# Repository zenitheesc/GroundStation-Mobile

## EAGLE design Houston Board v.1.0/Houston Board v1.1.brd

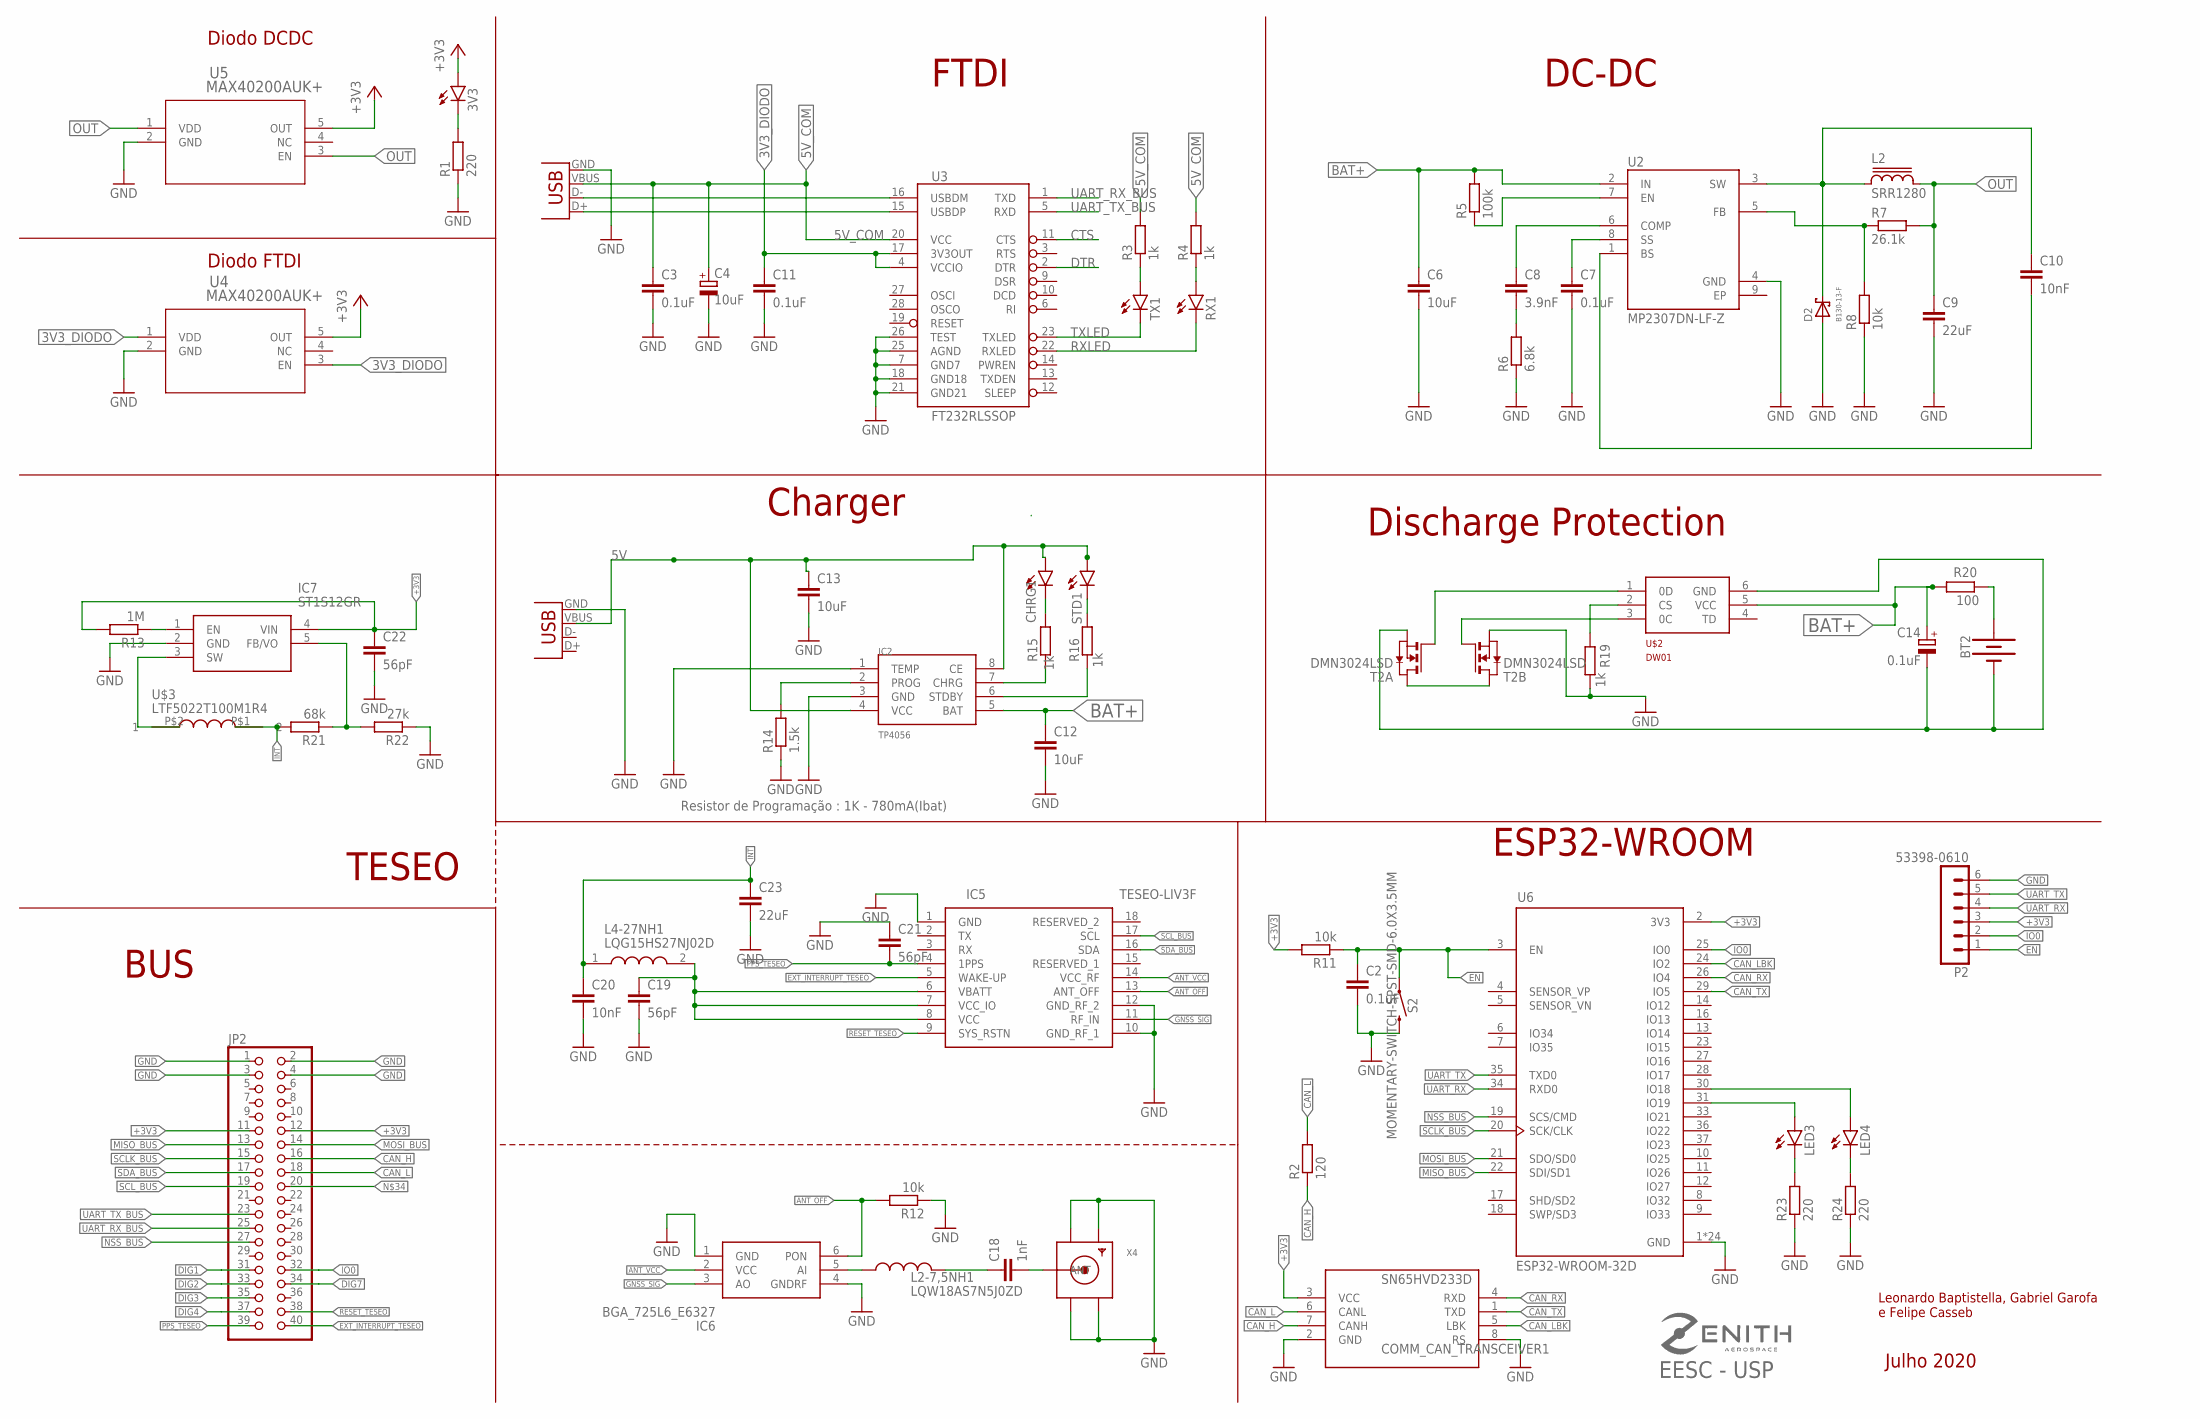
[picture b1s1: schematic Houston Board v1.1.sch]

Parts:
3V3: LEDCHIPLED_0805; CHIPLED_0805
BT2: BATTERY-18650; BATTERY_18650-HOLDER
C2: 0.1uF; C1206
C3, C7, C11: 0.1uF; C0805
C4: 10uF; PANASONIC_B
C6, C12, C13: 10uF; C0805
C8: 3.9nF; C0805
C9: 22uF; C0805
C10: 10nF; C0805
C14: 0.1uF; PANASONIC_C
C18: 1nF; C1206
C19, C21, C22: 56pF; C1206
C20: 10nF; C1206
C23: 22uF; C1206
CHRG1: LEDCHIP-LED0805; CHIP-LED0805
COMM_CAN_TRANSCEIVER1: SN65HVD233D; SOIC8
D2: B130-13-F; SMA
IC2: TP4056; SOP-8
IC5: TESEO-LIV3F; SON110P970X1010X230-18N
IC6: BGA_725L6_E6327; BGA725L6E6327
IC7: ST1S12GR; SOT95P280X110-5N
JP2: PINHD-2X20; 2X20
L2: SRR1280
L2-7,5NH1: LQW18AS7N5J0ZD; INDC1608X100N
L4-27NH1: LQG15HS27NJ02D; LQG15WH0N7B02D
LED3, LED4: LEDCHIPLED_0805; CHIPLED_0805
P2: 53398-0610
R1: 220; R0805
R2: 120; R0805
R3, R4, R15, R16, R19: 1k; R0805
R5: 100k; R0805
R6: 6.8k; R0805
R7: 26.1k; R0805
R8: 10k; R0805
R11: 10k; R1206
R12: 10k; M1206
R13: 1M; M1206
R14: 1.5k; R0805
R20: 100; R0805
R21: 68k; M1206
R22: 27k; M1206
R23, R24: 220; R1206
RX1: LEDCHIPLED_0805; CHIPLED_0805
S2: MOMENTARY-SWITCH-SPST-SMD-6.0X3.5MM; TACTILE_SWITCH_SMD_6.0X3.5MM
STD1: LEDCHIP-LED0805; CHIP-LED0805
T2: DMN3024LSD; TSSOP-8
TX1: LEDCHIPLED_0805; CHIPLED_0805
U2: MP2307DN-LF-Z; SOIC127P600X170-9N
U3: FT232RLSSOP; SSOP28DB
U4, U5: MAX40200AUK+; 21-0057F_MXM
U6: ESP32-WROOM-32D; MODULE_ESP32-WROOM-32D
U$2: DW01; SOT23-6
U$3: LTF5022T100M1R4; LTF5022T
X1, X2: USB-SMD-NS; USB-MINIB-NOSTOP
X4: SMACONNECTOR; SMA90_DIP

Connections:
3V3_DIODO: C11.1, U3.4 (VCCIO), U3.17 (3V3OUT), U4.1 (VDD), U4.3 (EN)
5V: C13.1, CHRG1.A, IC2.4 (VCC), IC2.8 (CE), STD1.A, X2.VBUS
5V_COM: C3.1, C4.+, R3.2, R4.2, U3.20 (VCC), X1.VBUS
+3V3: 3V3.A, C22.1, COMM_CAN_TRANSCEIVER1.3 (VCC), IC7.4 (VIN), JP2.11, JP2.12, P2.3, R11.2, R13.2, U4.5 (OUT), U5.5 (OUT), U6.2 (3V3)
ANT_OFF: IC5.13 (ANT_OFF), IC6.6 (PON), R12.2
ANT_VCC: IC5.14 (VCC_RF), IC6.2 (VCC)
BAT+: C6.1, C12.1, C14.+, IC2.5 (BAT), R5.2, R20.1, U2.2 (IN), U$2.5 (VCC)
CAN_H: COMM_CAN_TRANSCEIVER1.7 (CANH), JP2.16, R2.1
CAN_L: COMM_CAN_TRANSCEIVER1.6 (CANL), JP2.18, R2.2
CAN_LBK: COMM_CAN_TRANSCEIVER1.5 (LBK), U6.24 (IO2)
CAN_RX: COMM_CAN_TRANSCEIVER1.4 (RXD), U6.26 (IO4)
CAN_TX: COMM_CAN_TRANSCEIVER1.1 (TXD), U6.29 (IO5)
CTS: U3.11 (CTS)
DTR: U3.2 (DTR)
EN: C2.1, P2.1, R11.1, S2.1, U6.3 (EN)
EP: U2.9 (EP)
EXT_INTERRUPT_TESEO: IC5.5 (WAKE-UP), JP2.40
GND: C2.2, C3.2, C4.-, C6.2, C7.2, C9.2, C11.2, C12.2, C13.2, C19.2, C20.2, C21.1, C22.2, C23.2, COMM_CAN_TRANSCEIVER1.2 (GND), COMM_CAN_TRANSCEIVER1.8 (RS), D2.A, IC2.1 (TEMP), IC2.3 (GND), IC5.1 (GND), IC5.10 (GND_RF_1), IC5.12 (GND_RF_2), IC6.1 (GND), IC6.4 (GNDRF), IC7.2 (GND), JP2.1, JP2.2, JP2.3, JP2.4, P2.6, R1.1, R6.1, R8.1, R12.1, R14.1, R19.1, R22.1, R23.1, R24.1, S2.2, T2.6 (S), T2.7 (S), U2.4 (GND), U3.7 (GND7), U3.18 (GND18), U3.21 (GND21), U3.25 (AGND), U3.26 (TEST), U4.2 (GND), U5.2 (GND), U6.1 (GND), U6.15 (GND), U6.38 (GND), U6.39_1 (GND), U6.39_2 (GND), U6.39_3 (GND), U6.39_4 (GND), U6.39_5 (GND), U6.39_6 (GND), U6.39_7 (GND), U6.39_8 (GND), U6.39_9 (GND), U6.39_10 (GND), U6.39_11 (GND), U6.39_12 (GND), U6.39_13 (GND), U6.39_14 (GND), U6.39_15 (GND), U6.39_16 (GND), U6.39_17 (GND), U6.39_18 (GND), U6.39_19 (GND), U6.39_20 (GND), U6.39_21 (GND), X1.GND, X2.GND, X4.GND1, X4.GND2, X4.GND3, X4.GND4
GNSS_SIG: IC5.11 (RF_IN), IC6.3 (AO)
INT: C20.1, C23.1, L4-27NH1.1, R21.2, U$3.P$1 (2)
IO0: P2.2, U6.25 (IO0)
MISO_BUS: JP2.13, U6.22 (SDI/SD1)
MOSI_BUS: JP2.14, U6.21 (SDO/SD0)
unnamed: R5.1, U2.7 (EN)
unnamed: C8.2, R6.2
unnamed: C7.1, U2.8 (SS)
unnamed: C8.1, U2.6 (COMP)
unnamed: C10.1, D2.C, L2.1, U2.3 (SW)
unnamed: R7.1, R8.2, U2.5 (FB)
unnamed: C10.2, U2.1 (BS)
unnamed: R3.1, TX1.A
unnamed: R4.1, RX1.A
unnamed: 3V3.C, R1.2
unnamed: LED3.C, R23.2
unnamed: LED4.C, R24.2
unnamed: LED4.A, U6.30 (IO18)
unnamed: LED3.A, U6.31 (IO19)
unnamed: C19.1, IC5.6 (VBATT), IC5.7 (VCC_IO), IC5.8 (VCC), L4-27NH1.2
unnamed: C18.2, X4.ANTENNA (ANT)
unnamed: IC6.5 (AI), L2-7,5NH1.1
unnamed: IC2.2 (PROG), R14.2
unnamed: IC2.7 (CHRG), R15.1
unnamed: IC2.6 (STDBY), R16.1
unnamed: CHRG1.C, R15.2
unnamed: R16.2, STD1.C
unnamed: R19.2, U$2.2 (CS)
unnamed: BT2.PWR@1 (+), R20.2
unnamed: BT2.GND@1 (-), C14.-, T2.2 (S), T2.3 (S), U$2.6 (GND)
unnamed: T2.1 (D), T2.8 (D)
unnamed: T2.4 (G), U$2.1 (0D)
unnamed: T2.5 (G), U$2.3 (0C)
unnamed: C18.1, L2-7,5NH1.2
unnamed: IC7.1 (EN), R13.1
unnamed: IC7.3 (SW), U$3.P$2 (1)
unnamed: IC7.5 (FB/VO), R21.1, R22.2
NSS_BUS: JP2.27, U6.19 (SCS/CMD)
OUT: C9.1, L2.2, R7.2, U5.1 (VDD), U5.3 (EN)
PPS_TESEO: C21.2, IC5.4 (1PPS), JP2.39
RESET_TESEO: IC5.9 (SYS_RSTN), JP2.38
RXLED: RX1.C, U3.22 (RXLED)
SCLK_BUS: JP2.15, U6.20 (SCK/CLK)
SCL_BUS: IC5.17 (SCL), JP2.19
SDA_BUS: IC5.16 (SDA), JP2.17
TXLED: TX1.C, U3.23 (TXLED)
UART_RX: P2.4, U6.34 (RXD0)
UART_RX_BUS: JP2.25, U3.1 (TXD)
UART_TX: P2.5, U6.35 (TXD0)
UART_TX_BUS: JP2.23, U3.5 (RXD)
USB_D+1: U3.15 (USBDP), X1.D+
USB_D-1: U3.16 (USBDM), X1.D-

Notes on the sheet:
BUS
DC-DC
FTDI
Charger
Discharge Protection
TESEO
ESP32-WROOM
Resistor de Programação : 1K - 780mA(Ibat)
Diodo DCDC
Diodo FTDI
Julho 2020
Leonardo Baptistella, Gabriel Garofa e Felipe Casseb
EESC - USP

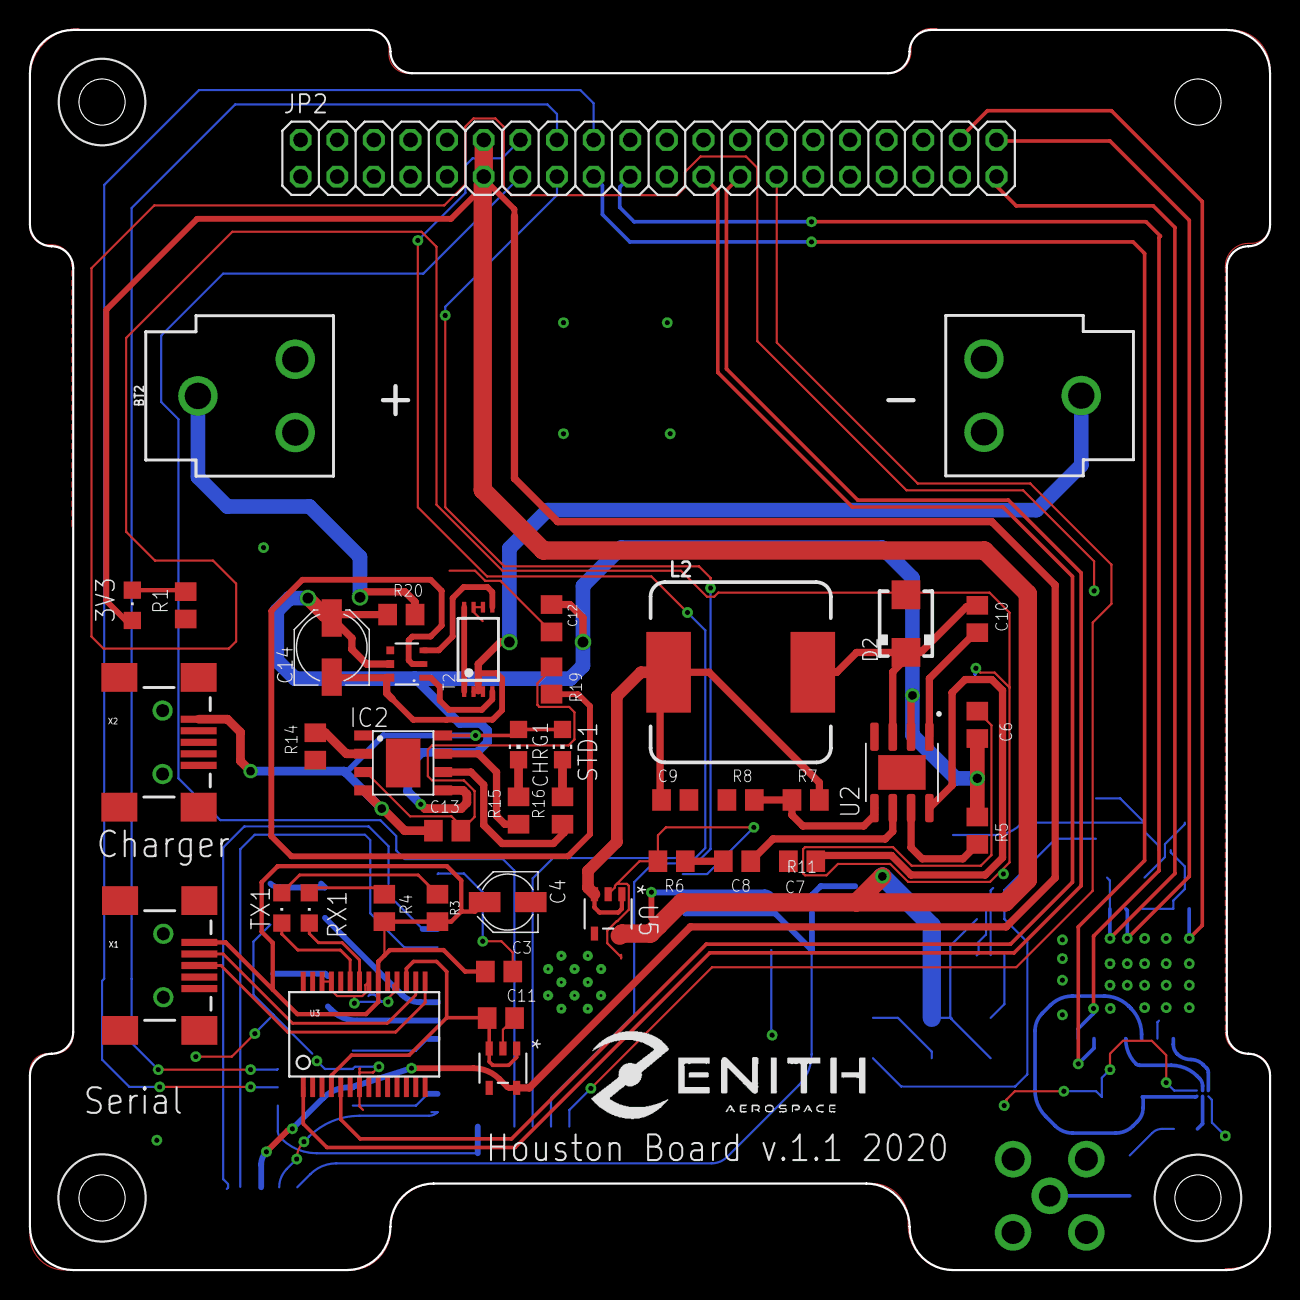
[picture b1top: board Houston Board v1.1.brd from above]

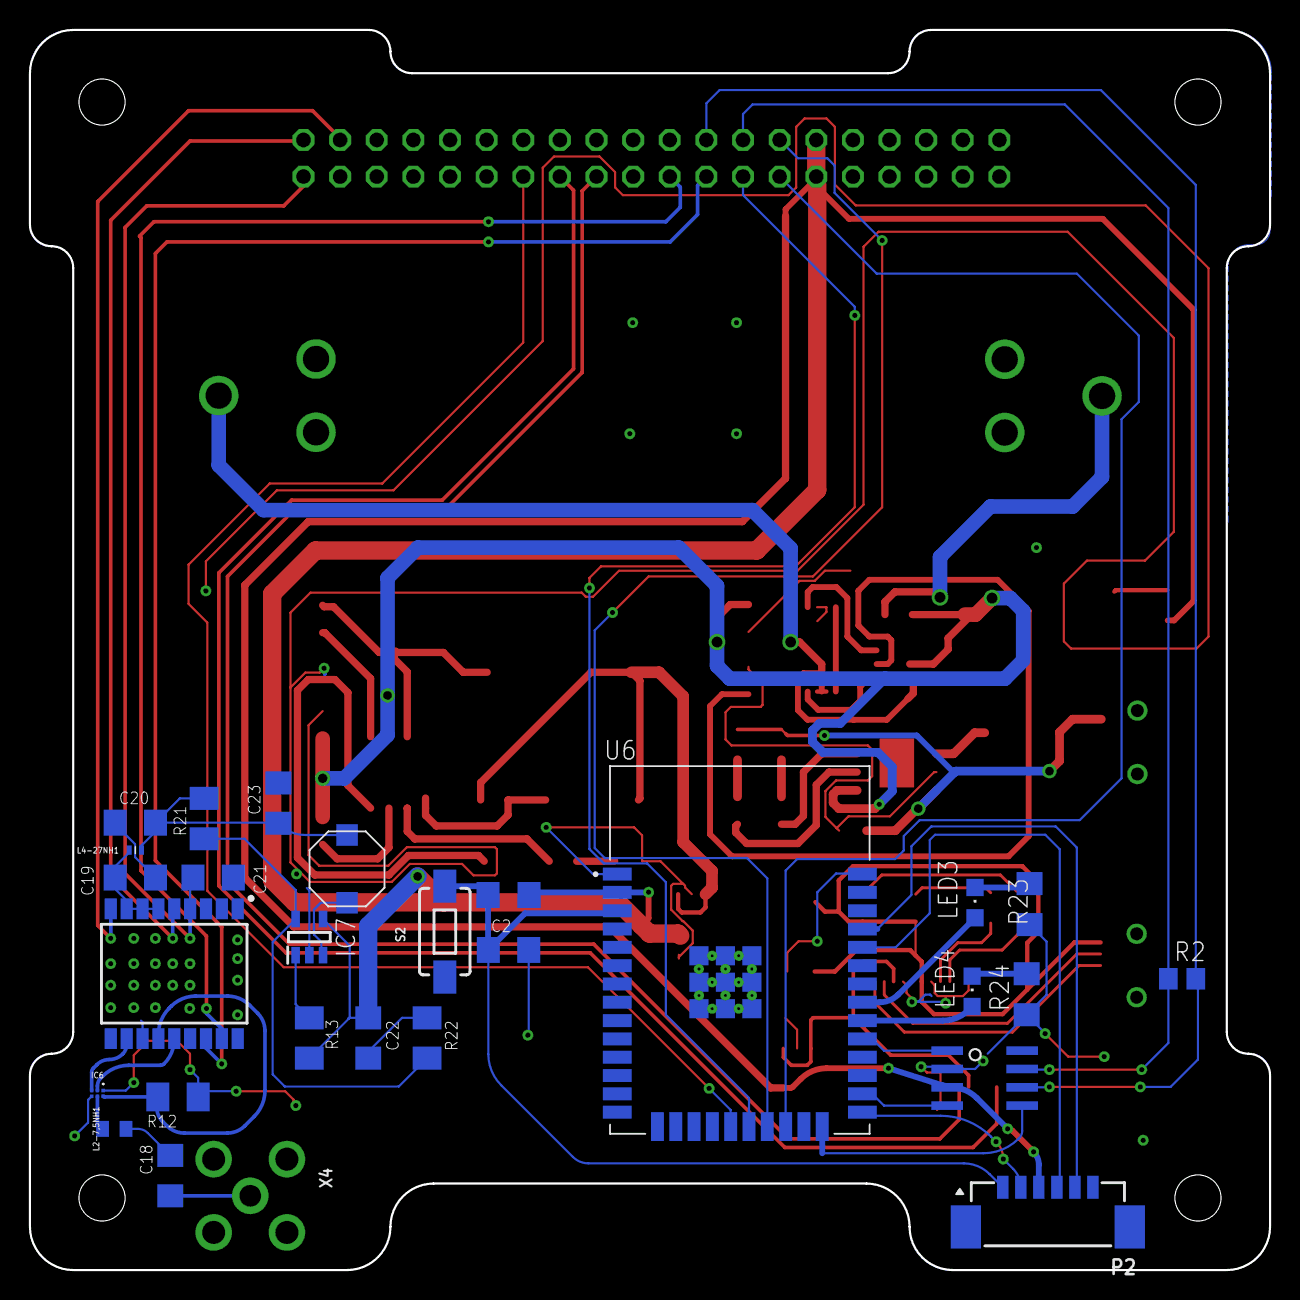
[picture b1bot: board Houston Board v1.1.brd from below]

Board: 2 copper layers, 86.0 x 86.0 mm, 69 parts (28 on the bottom side), 67 nets.

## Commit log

2020-08-02 first version
2020-08-02 Gerber
2020-08-02 Correção de Erros

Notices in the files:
parts and their libraries:
inductor-bourns: Copyright (C) 2008, Bob Starr
SparkFun-Batteries: Licensing: Creative Commons ShareAlike 4.0 International - https://creativecommons.org/licenses/by-sa/4.0
con-molex-picoblade: Copyright (C) 2010, Bob Starr
COPYRIGHT: Copyright (C) 2018 Accelerated Designs. All rights reserved
